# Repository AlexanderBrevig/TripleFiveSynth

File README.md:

# TripleFiveSynth

    Work In Progress!

A simple idea of using a 555 timer per note in a synth.

## `/src/main.rs`

This will generate appropriate capacitor and trim values for each note.

See the output in [tune_triple_fives.txt](https://raw.githubusercontent.com/alexanderbrevig/TripleFiveSynth/tune_triple_fives.txt) for details.

## 555 Configuration

The plan is to have one of these voices per note:

## Example tuning for 440Hz

Per the line in `tune_triple_fives.txt` we get:

> 0440.00Hz => 150.00nF	Trim => 1431.9Ω -> 71.60%

This means, our `C3` should be `150nF`, and `R3` at approx `71.6%`.

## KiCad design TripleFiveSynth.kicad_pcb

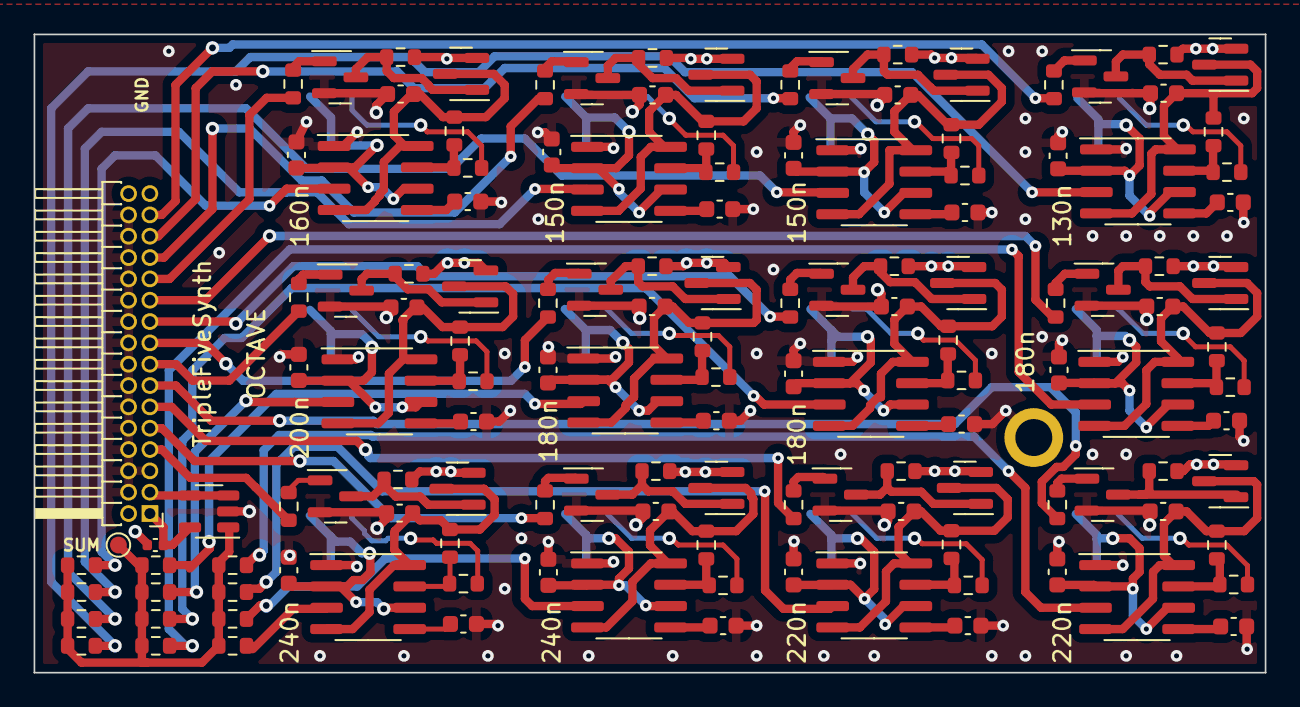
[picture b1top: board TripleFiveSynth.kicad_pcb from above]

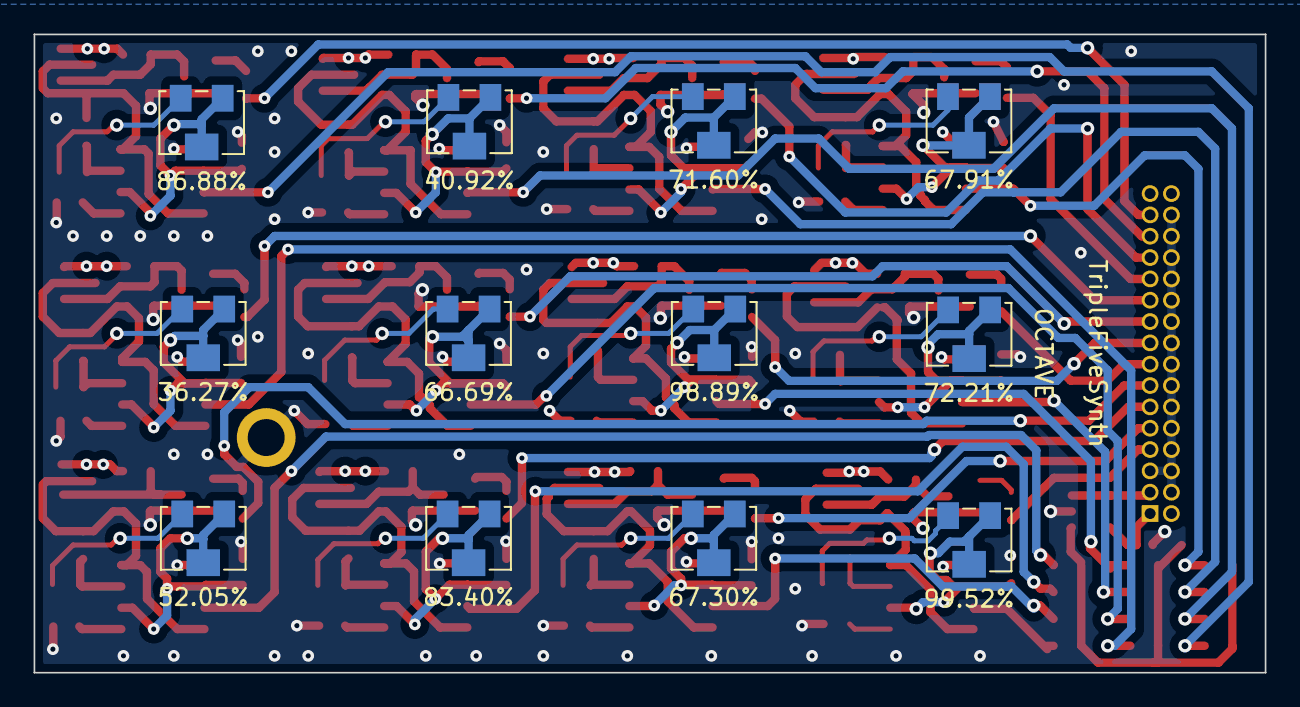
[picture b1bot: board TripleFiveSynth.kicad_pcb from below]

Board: 4 copper layers, 73.3 x 38.0 mm, 149 parts (12 on the bottom side), 112 nets.

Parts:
C101: 100n; C_0402_1005Metric
C201, C301, C401, C501, C601, C701, C801, C901, C1001, C1101, C1201, C1301: 100n; C_0603_1608Metric
C202, C302, C402, C502, C602, C702, C802, C902, C1002, C1102, C1202, C1302: 0.01u; C_0603_1608Metric
C203, C303, C403, C503, C603, C703, C803, C903, C1003, C1103, C1203, C1303: ${c_val}; C_0603_1608Metric
H101: MountingHole_Pad; MountingHole_2.2mm_M2_ISO7380_Pad
J101: OctaveIO; PinHeader_2x16_P1.27mm_Horizontal
Q201, Q301, Q401, Q501, Q601, Q701, Q801, Q901, Q1001, Q1101, Q1201, Q1301: MMBT3904; SOT-23
Q202, Q302, Q402, Q502, Q602, Q702, Q802, Q902, Q1002, Q1102, Q1202, Q1302: BSS84; SOT-23
R101, R102, R103, R104, R105, R106, R107, R108, R109, R110, R111, R112, R201, R202, R301, R302, R401, R402, R501, R502, R601, R602, R701, R702, R801, R802, R901, R902, R1001, R1002, R1101, R1102, R1201, R1202, R1301, R1302: 10k; R_0603_1608Metric
R203, R303, R403, R503, R603, R703, R803, R903, R1003, R1103, R1203, R1303: 1k; R_0603_1608Metric
R204, R304, R404, R504, R604, R704, R804, R904, R1004, R1104, R1204, R1304: 9k; R_0603_1608Metric
TP101: SUM; TestPoint_Pad_D1.0mm
TR201, TR301, TR401, TR501, TR601, TR701, TR801, TR901, TR1001, TR1101, TR1201, TR1301: ${r_val}; Potentiometer_Bourns_3224W_Vertical
U101: LMV321; SOT-23-5
U201, U301, U401, U501, U601, U701, U801, U901, U1001, U1101, U1201, U1301: NE555D; SOIC-8_3.9x4.9mm_P1.27mm

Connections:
+5V: C101.1, J101.1, J101.2, J101.31, J101.32, Q202.2 (S), Q302.2 (S), Q402.2 (S), Q502.2 (S), Q602.2 (S), Q702.2 (S), Q802.2 (S), Q902.2 (S), Q1002.2 (S), Q1102.2 (S), Q1202.2 (S), Q1302.2 (S), R202.1, R302.1, R402.1, R502.1, R602.1, R702.1, R802.1, R902.1, R1002.1, R1102.1, R1202.1, R1302.1, U101.5 (V+)
/GATEA: J101.25, R1101.2
/GATEAS: J101.27, R1001.2
/GATEB: J101.29, R1201.2
/GATEC: J101.7, R401.2
/GATECS: J101.9, R301.2
/GATED: J101.11, R201.2
/GATEDS: J101.13, R1301.2
/GATEE: J101.15, R501.2
/GATEF: J101.17, R701.2
/GATEFS: J101.19, R601.2
/GATEG: J101.21, R801.2
/GATEGS: J101.23, R901.2
/OUTA: R110.2, U1101.3 (Q)
/OUTAS: R111.2, U1001.3 (Q)
/OUTB: R112.2, U1201.3 (Q)
/OUTC: R101.2, U401.3 (Q)
/OUTCS: R102.2, U301.3 (Q)
/OUTD: R103.2, U201.3 (Q)
/OUTDS: R104.2, U1301.3 (Q)
/OUTE: R105.2, U501.3 (Q)
/OUTEG: R108.2, U801.3 (Q)
/OUTF: R106.2, U701.3 (Q)
/OUTFS: R107.2, U601.3 (Q)
/OUTGS: R109.2, U901.3 (Q)
/OUTSUM: J101.3, U101.3 (-), U101.4
/SUM: R101.1, R102.1, R103.1, R104.1, R105.1, R106.1, R107.1, R108.1, R109.1, R110.1, R111.1, R112.1, TP101.1, U101.1 (+)
/Voice1/555PWR: C301.1, Q302.3 (D), R303.2, U301.4 (R), U301.8 (VCC)
/Voice1/CV: C302.1, U301.5 (CV)
/Voice1/DIS: R303.1, R304.2, U301.7 (DIS)
/Voice1/SWEN: Q301.3 (C), Q302.1 (G), R302.2
/Voice1/TR: C303.1, TR301.1, TR301.2, U301.2 (TR), U301.6 (THR)
/Voice2/555PWR: C201.1, Q202.3 (D), R203.2, U201.4 (R), U201.8 (VCC)
/Voice2/CV: C202.1, U201.5 (CV)
/Voice2/DIS: R203.1, R204.2, U201.7 (DIS)
/Voice2/SWEN: Q201.3 (C), Q202.1 (G), R202.2
/Voice2/TR: C203.1, TR201.1, TR201.2, U201.2 (TR), U201.6 (THR)
/Voice3/555PWR: C1301.1, Q1302.3 (D), R1303.2, U1301.4 (R), U1301.8 (VCC)
/Voice3/CV: C1302.1, U1301.5 (CV)
/Voice3/DIS: R1303.1, R1304.2, U1301.7 (DIS)
/Voice3/SWEN: Q1301.3 (C), Q1302.1 (G), R1302.2
/Voice3/TR: C1303.1, TR1301.1, TR1301.2, U1301.2 (TR), U1301.6 (THR)
/Voice4/555PWR: C601.1, Q602.3 (D), R603.2, U601.4 (R), U601.8 (VCC)
/Voice4/CV: C602.1, U601.5 (CV)
/Voice4/DIS: R603.1, R604.2, U601.7 (DIS)
/Voice4/SWEN: Q601.3 (C), Q602.1 (G), R602.2
/Voice4/TR: C603.1, TR601.1, TR601.2, U601.2 (TR), U601.6 (THR)
/Voice5/555PWR: C501.1, Q502.3 (D), R503.2, U501.4 (R), U501.8 (VCC)
/Voice5/CV: C502.1, U501.5 (CV)
/Voice5/DIS: R503.1, R504.2, U501.7 (DIS)
/Voice5/SWEN: Q501.3 (C), Q502.1 (G), R502.2
/Voice5/TR: C503.1, TR501.1, TR501.2, U501.2 (TR), U501.6 (THR)
/Voice6/555PWR: C701.1, Q702.3 (D), R703.2, U701.4 (R), U701.8 (VCC)
/Voice6/CV: C702.1, U701.5 (CV)
/Voice6/DIS: R703.1, R704.2, U701.7 (DIS)
/Voice6/SWEN: Q701.3 (C), Q702.1 (G), R702.2
/Voice6/TR: C703.1, TR701.1, TR701.2, U701.2 (TR), U701.6 (THR)
/Voice7/555PWR: C801.1, Q802.3 (D), R803.2, U801.4 (R), U801.8 (VCC)
/Voice7/CV: C802.1, U801.5 (CV)
/Voice7/DIS: R803.1, R804.2, U801.7 (DIS)
/Voice7/SWEN: Q801.3 (C), Q802.1 (G), R802.2
/Voice7/TR: C803.1, TR801.1, TR801.2, U801.2 (TR), U801.6 (THR)
/Voice8/555PWR: C1201.1, Q1202.3 (D), R1203.2, U1201.4 (R), U1201.8 (VCC)
/Voice8/CV: C1202.1, U1201.5 (CV)
/Voice8/DIS: R1203.1, R1204.2, U1201.7 (DIS)
/Voice8/SWEN: Q1201.3 (C), Q1202.1 (G), R1202.2
/Voice8/TR: C1203.1, TR1201.1, TR1201.2, U1201.2 (TR), U1201.6 (THR)
/Voice9/555PWR: C901.1, Q902.3 (D), R903.2, U901.4 (R), U901.8 (VCC)
/Voice9/CV: C902.1, U901.5 (CV)
/Voice9/DIS: R903.1, R904.2, U901.7 (DIS)
/Voice9/SWEN: Q901.3 (C), Q902.1 (G), R902.2
/Voice9/TR: C903.1, TR901.1, TR901.2, U901.2 (TR), U901.6 (THR)
/Voice10/555PWR: C1101.1, Q1102.3 (D), R1103.2, U1101.4 (R), U1101.8 (VCC)
/Voice10/CV: C1102.1, U1101.5 (CV)
/Voice10/DIS: R1103.1, R1104.2, U1101.7 (DIS)
/Voice10/SWEN: Q1101.3 (C), Q1102.1 (G), R1102.2
/Voice10/TR: C1103.1, TR1101.1, TR1101.2, U1101.2 (TR), U1101.6 (THR)
/Voice11/555PWR: C1001.1, Q1002.3 (D), R1003.2, U1001.4 (R), U1001.8 (VCC)
/Voice11/CV: C1002.1, U1001.5 (CV)
/Voice11/DIS: R1003.1, R1004.2, U1001.7 (DIS)
/Voice11/SWEN: Q1001.3 (C), Q1002.1 (G), R1002.2
/Voice11/TR: C1003.1, TR1001.1, TR1001.2, U1001.2 (TR), U1001.6 (THR)
/Voice/555PWR: C401.1, Q402.3 (D), R403.2, U401.4 (R), U401.8 (VCC)
/Voice/CV: C402.1, U401.5 (CV)
/Voice/DIS: R403.1, R404.2, U401.7 (DIS)
/Voice/SWEN: Q401.3 (C), Q402.1 (G), R402.2
/Voice/TR: C403.1, TR401.1, TR401.2, U401.2 (TR), U401.6 (THR)
GND: C101.2, C201.2, C202.2, C203.2, C301.2, C302.2, C303.2, C401.2, C402.2, C403.2, C501.2, C502.2, C503.2, C601.2, C602.2, C603.2, C701.2, C702.2, C703.2, C801.2, C802.2, C803.2, C901.2, C902.2, C903.2, C1001.2, C1002.2, C1003.2, C1101.2, C1102.2, C1103.2, C1201.2, C1202.2, C1203.2, C1301.2, C1302.2, C1303.2, H101.1, J101.4, J101.5, J101.6, J101.8, J101.10, J101.12, J101.14, J101.16, J101.18, J101.20, J101.22, J101.24, J101.26, J101.28, J101.30, Q201.2 (E), Q301.2 (E), Q401.2 (E), Q501.2 (E), Q601.2 (E), Q701.2 (E), Q801.2 (E), Q901.2 (E), Q1001.2 (E), Q1101.2 (E), Q1201.2 (E), Q1301.2 (E), U101.2 (V-), U201.1 (GND), U301.1 (GND), U401.1 (GND), U501.1 (GND), U601.1 (GND), U701.1 (GND), U801.1 (GND), U901.1 (GND), U1001.1 (GND), U1101.1 (GND), U1201.1 (GND), U1301.1 (GND)
unnamed: Q201.1 (B), R201.1
unnamed: Q301.1 (B), R301.1
unnamed: Q401.1 (B), R401.1
unnamed: Q501.1 (B), R501.1
unnamed: Q601.1 (B), R601.1
unnamed: Q701.1 (B), R701.1
unnamed: Q801.1 (B), R801.1
unnamed: Q901.1 (B), R901.1
unnamed: Q1001.1 (B), R1001.1
unnamed: Q1101.1 (B), R1101.1
unnamed: Q1201.1 (B), R1201.1
unnamed: Q1301.1 (B), R1301.1
unnamed: R204.1, TR201.3
unnamed: R304.1, TR301.3
unnamed: R404.1, TR401.3
unnamed: R504.1, TR501.3
unnamed: R604.1, TR601.3
unnamed: R704.1, TR701.3
unnamed: R804.1, TR801.3
unnamed: R904.1, TR901.3
unnamed: R1004.1, TR1001.3
unnamed: R1104.1, TR1101.3
unnamed: R1204.1, TR1201.3
unnamed: R1304.1, TR1301.3

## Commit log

2022-02-02 initial commit, cap + trim calc working
2022-02-02 fix image
2022-02-02 add note for tuning 440Hz
2022-02-02 ERC and DRC 0 errors
2022-02-02 swap to SMD Bourns 3224W, can stack in Eurorack now
2022-02-04 sim with correct components, and 5V
2022-02-04 cleanup sim folder
2022-02-04 update with 5V and on-board sum
2022-02-04 add schematic for easier review
2022-02-04 update gitignore with LTSpice
2022-02-04 ignore LTSpice plt
